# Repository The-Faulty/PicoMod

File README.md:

# PicoMod
PicoMod is an RP2040-based compute module with high density connectors allowing for its small 20mmx20mm form-factor.

# PicoMod Breakout
This is a breakout for PicoMod to allowing use on a standard breadboard.

# PicoMod Eject
Eject is the evolution of [Lyra](https://github.com/The_Faulty/Lyra) maintaining Lyra's small size while greatly improving the power and sensing abilities. Not only can eject ignite an e-match at apogee, it also contains a 9-DOF sensor suite and two servo outputs enabling TVC (thrust vector control) usage.

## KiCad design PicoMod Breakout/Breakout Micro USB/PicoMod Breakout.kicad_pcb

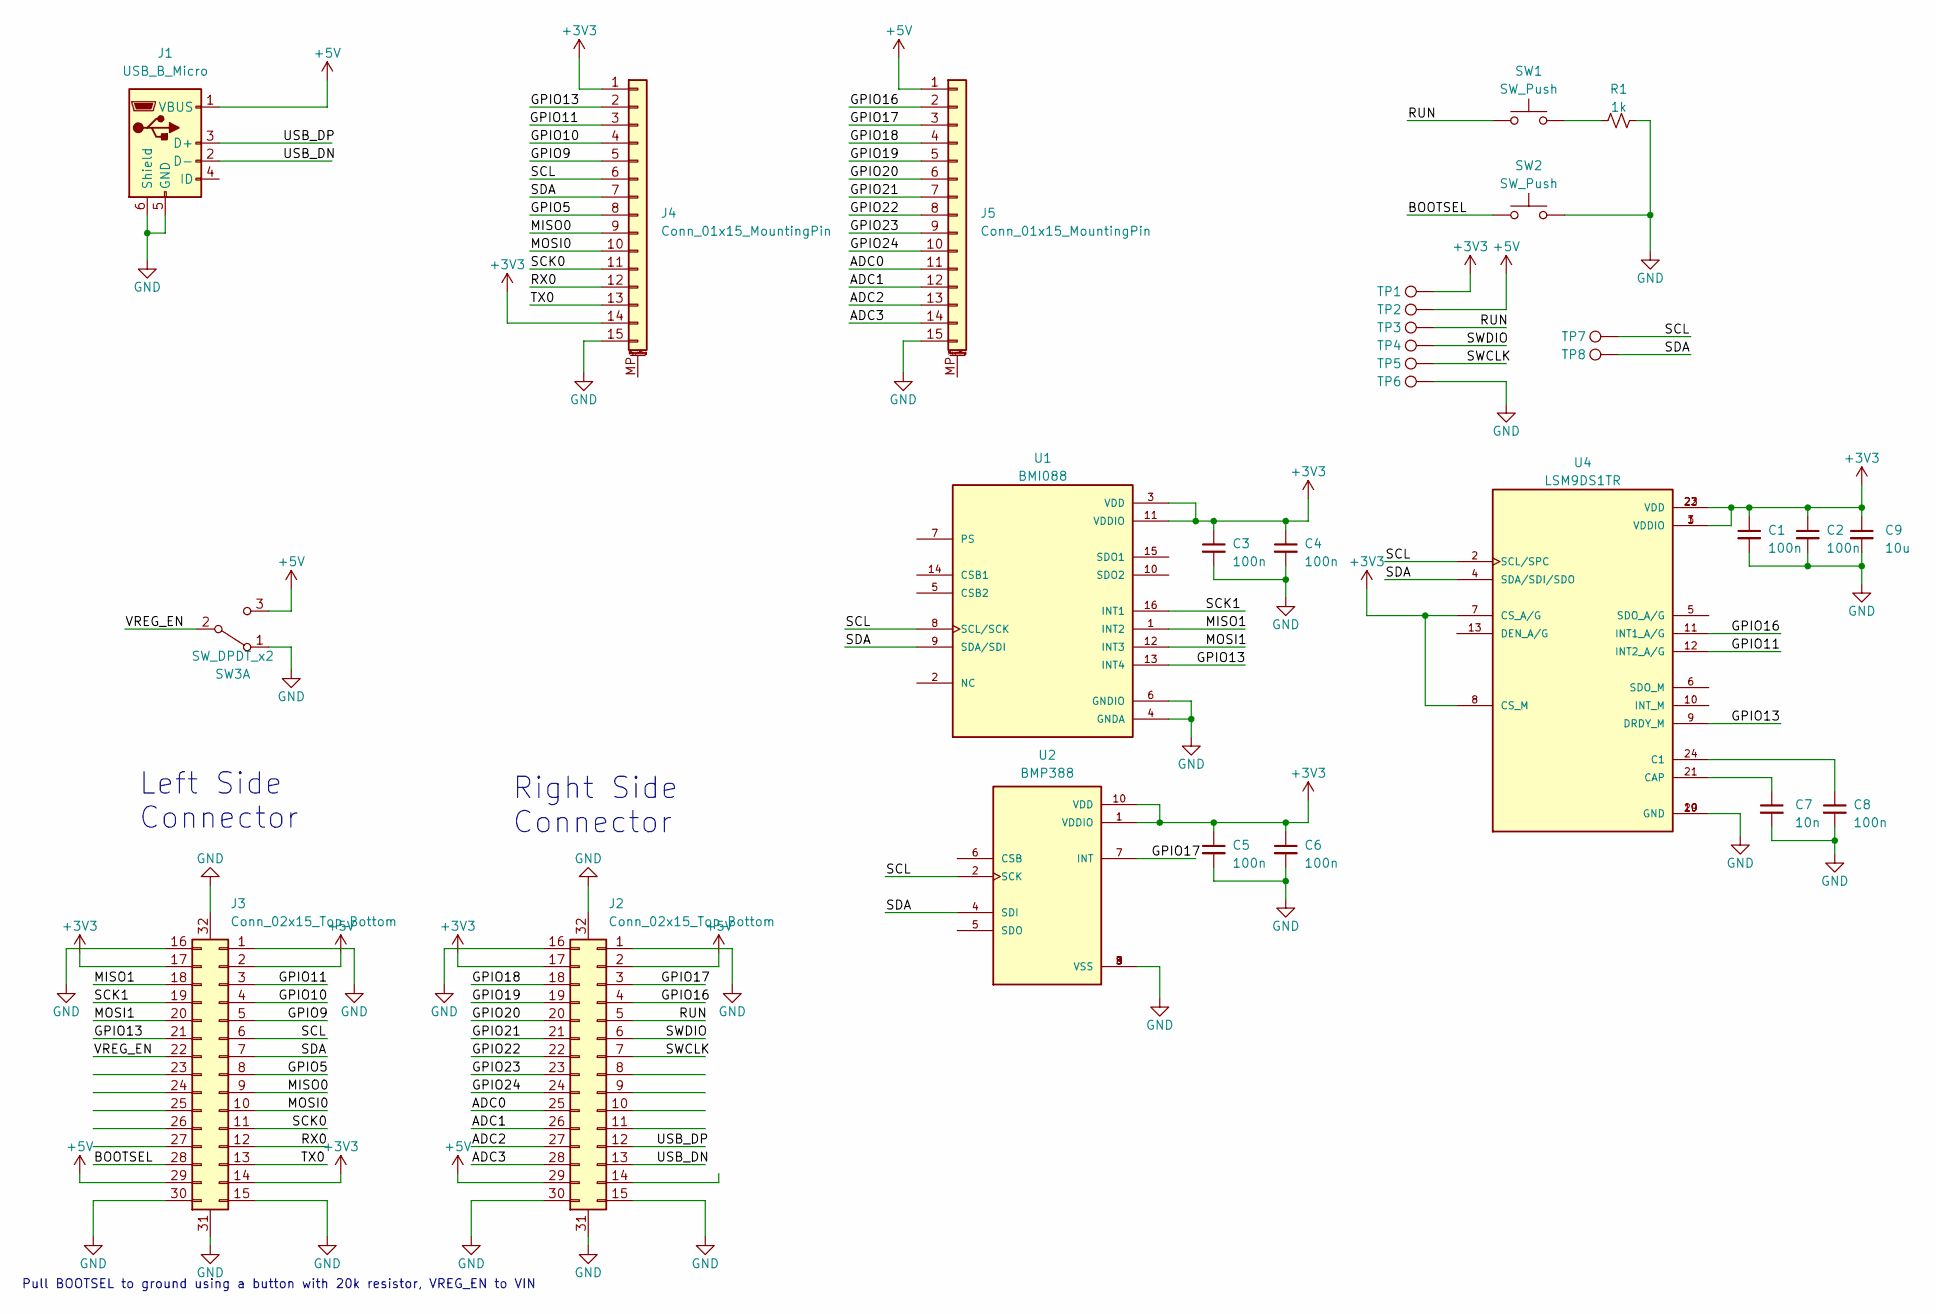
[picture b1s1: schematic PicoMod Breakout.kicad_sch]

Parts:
C1, C2, C3, C4, C5, C6, C8: 100n; C_0603_1608Metric
C7: 10n; C_0603_1608Metric
C9: 10u; C_0603_1608Metric
J1: USB_B_Micro; USB_Micro-B_Amphenol_10104110_Horizontal
J2, J3: Conn_02x15_Top_Bottom; TE-3-2363962-0_30x0.4mm_Recepticle
J4, J5: Conn_01x15_MountingPin; PinSocket_1x15_P2.54mm_Vertical
R1: 1k; R_0603_1608Metric_Pad0.98x0.95mm_HandSolder
SW1, SW2: SW_Push; PTS815 SJM 250
SW3: SW_DPDT_x2; SPDT_Switch_AYZ0102AGRLC
TP1, TP2, TP3, TP4, TP5, TP6, TP7, TP8: TestPoint; TestPoint_Loop_1.6x0.8mm
U1: BMI088; PQFN50P450X300X100-16N
U2: BMP388; PQFN50P200X200X80-10N; PARTREV 1.1
U4: LSM9DS1TR; PQFN43P300X350X102-24N; PARTREV 3

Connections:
+3V3: C1.1, C2.1, C3.1, C4.1, C5.1, C6.1, C9.1, J2.17, J3.14, J3.17, J4.1, J4.14, TP1.1, U1.3 (VDD), U1.11 (VDDIO), U2.1 (VDDIO), U2.10 (VDD), U4.1 (VDDIO), U4.3 (VDDIO), U4.7 (CS_A/G), U4.8 (CS_M), U4.22 (VDD), U4.23 (VDD)
+5V: J1.1 (VBUS), J2.2, J2.29, J3.2, J3.29, J5.1, SW3.3 (C), TP2.1
/ADC0: J2.25, J5.11
/ADC1: J2.26, J5.12
/ADC2: J2.27, J5.13
/ADC3: J2.28, J5.14
/BOOTSEL: J3.28, SW2.1
/GPIO5: J3.8, J4.8
/GPIO9: J3.5, J4.5
/GPIO10: J3.4, J4.4
/GPIO11: J3.3, J4.3, U4.12 (INT2_A/G)
/GPIO13: J3.21, J4.2, U1.13 (INT4), U4.9 (DRDY_M)
/GPIO16: J2.4, J5.2, U4.11 (INT1_A/G)
/GPIO17: J2.3, J5.3, U2.7 (INT)
/GPIO18: J2.18, J5.4
/GPIO19: J2.19, J5.5
/GPIO20: J2.20, J5.6
/GPIO21: J2.21, J5.7
/GPIO22: J2.22, J5.8
/GPIO23: J2.23, J5.9
/GPIO24: J2.24, J5.10
/MISO0: J3.9, J4.9
/MISO1: J3.18, U1.1 (INT2)
/MOSI0: J3.10, J4.10
/MOSI1: J3.20, U1.12 (INT3)
/RUN: J2.5, SW1.1, TP3.1
/RX0: J3.12, J4.12
/SCK0: J3.11, J4.11
/SCK1: J3.19, U1.16 (INT1)
/SCL: J3.6, J4.6, TP7.1, U1.8 (SCL/SCK), U2.2 (SCK), U4.2 (SCL/SPC)
/SDA: J3.7, J4.7, TP8.1, U1.9 (SDA/SDI), U2.4 (SDI), U4.4 (SDA/SDI/SDO)
/SWCLK: J2.7, TP5.1
/SWDIO: J2.6, TP4.1
/TX0: J3.13, J4.13
/USB_DN: J1.2 (D-), J2.13
/USB_DP: J1.3 (D+), J2.12
/VREG_EN: J3.22, SW3.2 (B)
GND: C1.2, C2.2, C3.2, C4.2, C5.2, C6.2, C7.2, C8.2, C9.2, J1.5 (GND), J1.6 (Shield), J2.1, J2.15, J2.16, J2.30, J2.31 (Pin_30), J2.32 (Pin_30), J3.1, J3.15, J3.16, J3.30, J3.31 (Pin_30), J3.32 (Pin_30), J4.15, J5.15, R1.2, SW2.2, SW3.1 (A), TP6.1, U1.4 (GNDA), U1.6 (GNDIO), U2.3 (VSS), U2.8 (VSS), U2.9 (VSS), U4.19 (GND), U4.20 (GND)
unnamed: R1.1, SW1.2
unnamed: C8.1, U4.24 (C1)
unnamed: C7.1, U4.21 (CAP)

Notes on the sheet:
Left Side Connector
Right Side Connector
Pull BOOTSEL to ground using a button with 20k resistor, VREG_EN to VIN

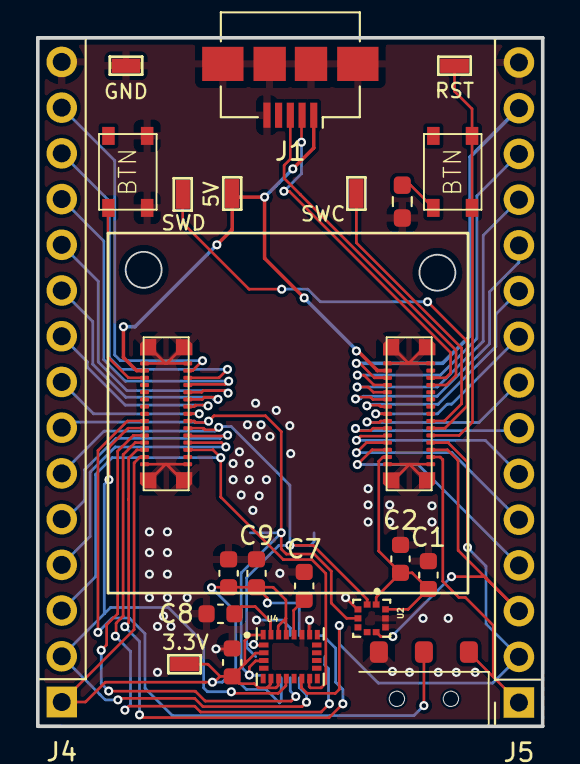
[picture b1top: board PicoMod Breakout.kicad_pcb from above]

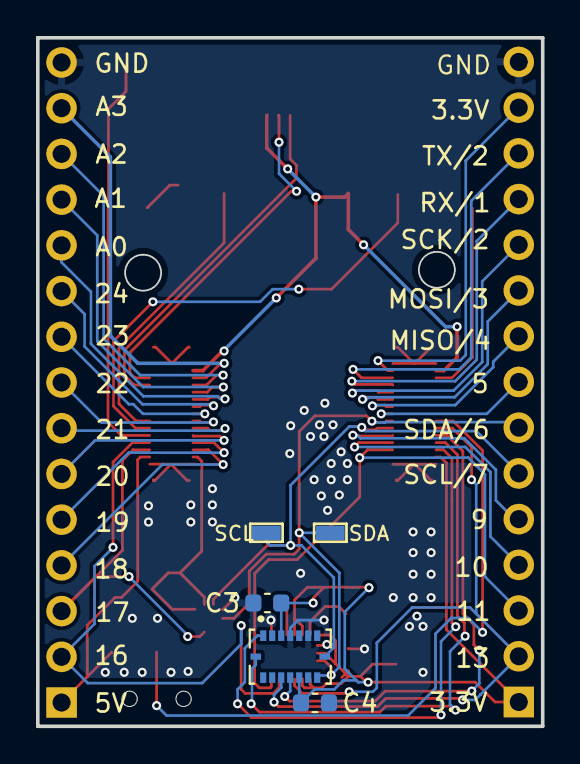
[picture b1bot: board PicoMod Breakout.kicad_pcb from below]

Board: 2 copper layers, 28.0 x 38.3 mm, 29 parts (5 on the bottom side), 41 nets.

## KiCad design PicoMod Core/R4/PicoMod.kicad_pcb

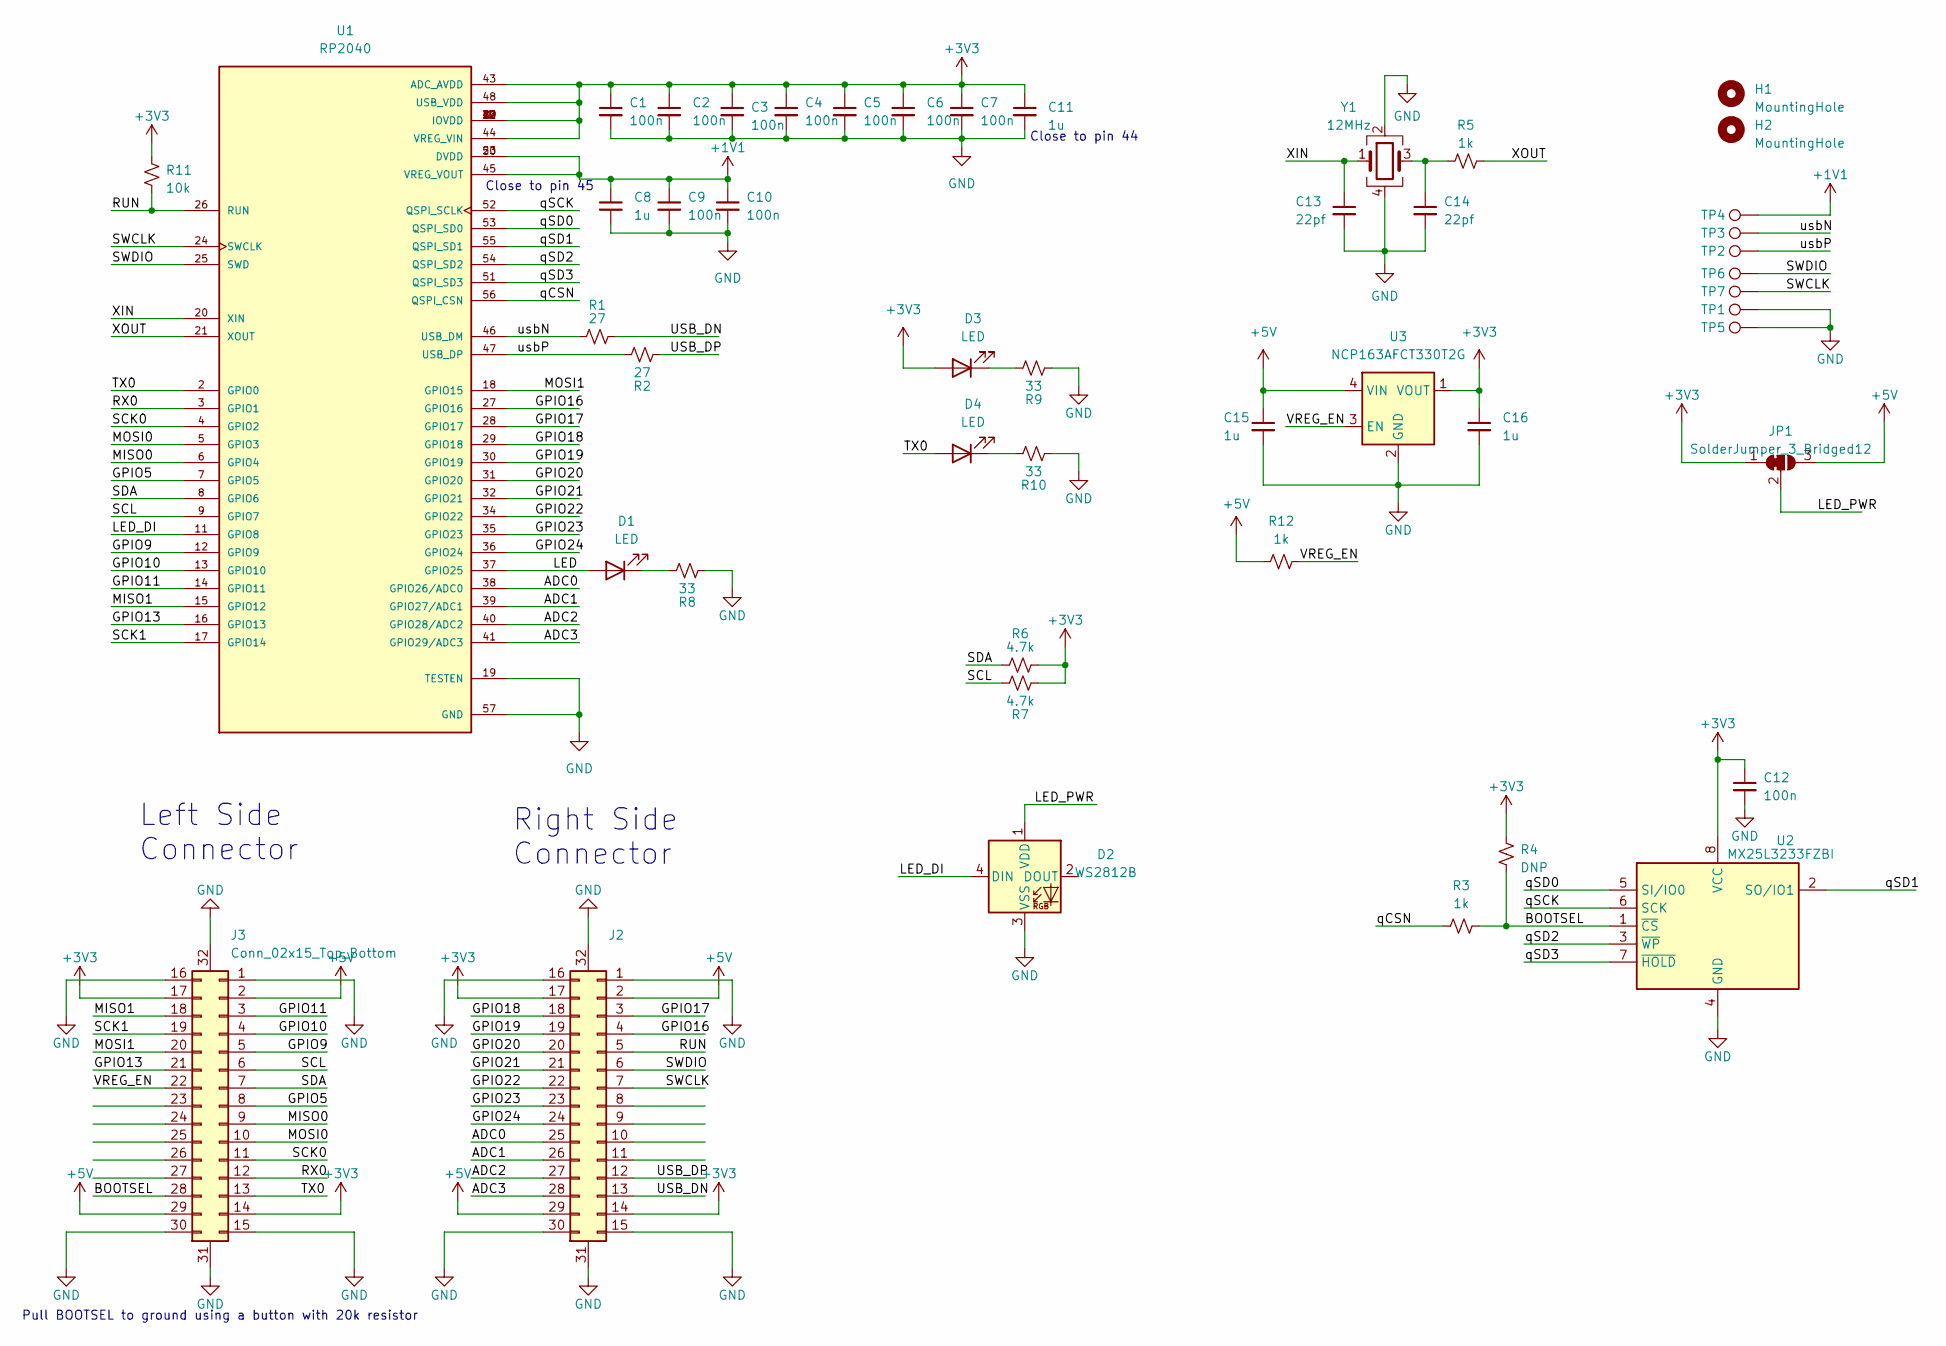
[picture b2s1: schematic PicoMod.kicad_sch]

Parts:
C1, C2, C3, C4, C5, C6, C7, C9, C10, C12: 100n; C_0603_1608Metric
C8, C11, C15, C16: 1u; C_0603_1608Metric
C13, C14: 22pf; C_0603_1608Metric
D1, D3, D4: LED; LED_0603_1608Metric
D2: WS2812B; LED_WS2812B_PLCC4_2.0x2.0mm_P0.4mm
H1, H2: MountingHole; MountingHole_2mm_M2
J2, J3: Conn_02x15_Top_Bottom; TE-3-2363962-0_30x0.4mm_Plug
JP1: SolderJumper_3_Bridged12; SolderJumper-3_P1.3mm_Open_RoundedPad1.0x1.5mm
R1, R2: 27; R_0402_1005Metric
R3, R5, R12: 1k; R_0402_1005Metric
R4: DNP; R_0603_1608Metric
R6, R7: 4.7k; R_0603_1608Metric
R8, R9, R10: 33; R_0402_1005Metric
R11: 10k; R_0603_1608Metric
TP1: TestPoint; TestPoint_Loop_1.6x0.8mm
TP2, TP3, TP4, TP5, TP6, TP7: TestPoint; TestPoint_Pad_D1.0mm
U1: RP2040; QFN40P700X700X90-57N; PARTREV 1.6.1
U2: MX25L3233FZBI; SON80P400X300X60-10N
U3: NCP163AFCT330T2G; OnSemi_XDFN4-1EP_1.0x1.0mm_EP0.52x0.52mm
Y1: 12MHz; Crystal_SMD_SeikoEpson_TSX3225-4Pin_3.2x2.5mm

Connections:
+1V1: C8.1, C9.1, C10.1, TP4.1, U1.23 (DVDD), U1.45 (VREG_VOUT), U1.50 (DVDD)
+3V3: C1.1, C2.1, C3.1, C4.1, C5.1, C6.1, C7.1, C11.1, C12.1, C16.1, D3.2 (A), J2.14, J2.17, J3.14, J3.17, JP1.1 (A), R4.2, R6.2, R7.2, R11.2, U1.1 (IOVDD), U1.10 (IOVDD), U1.22 (IOVDD), U1.33 (IOVDD), U1.42 (IOVDD), U1.43 (ADC_AVDD), U1.44 (VREG_VIN), U1.48 (USB_VDD), U1.49 (IOVDD), U2.8 (VCC), U3.1 (VOUT)
+5V: C15.1, J2.2, J2.29, J3.2, J3.29, JP1.3 (B), R12.1, U3.4 (VIN)
/ADC0: J2.25, U1.38 (GPIO26/ADC0)
/ADC1: J2.26, U1.39 (GPIO27/ADC1)
/ADC2: J2.27, U1.40 (GPIO28/ADC2)
/ADC3: J2.28, U1.41 (GPIO29/ADC3)
/BOOTSEL: J3.28, R3.2, R4.1, U2.1 (~CS)
/GPIO5: J3.8, U1.7 (GPIO5)
/GPIO9: J3.5, U1.12 (GPIO9)
/GPIO10: J3.4, U1.13 (GPIO10)
/GPIO11: J3.3, U1.14 (GPIO11)
/GPIO13: J3.21, U1.16 (GPIO13)
/GPIO16: J2.4, U1.27 (GPIO16)
/GPIO17: J2.3, U1.28 (GPIO17)
/GPIO18: J2.18, U1.29 (GPIO18)
/GPIO19: J2.19, U1.30 (GPIO19)
/GPIO20: J2.20, U1.31 (GPIO20)
/GPIO21: J2.21, U1.32 (GPIO21)
/GPIO22: J2.22, U1.34 (GPIO22)
/GPIO23: J2.23, U1.35 (GPIO23)
/GPIO24: J2.24, U1.36 (GPIO24)
/LED: D1.2 (A), U1.37 (GPIO25)
/LED_DI: D2.4 (DIN), U1.11 (GPIO8)
/LED_PWR: D2.1 (VDD), JP1.2 (C)
/MISO0: J3.9, U1.6 (GPIO4)
/MISO1: J3.18, U1.15 (GPIO12)
/MOSI0: J3.10, U1.5 (GPIO3)
/MOSI1: J3.20, U1.18 (GPIO15)
/RUN: J2.5, R11.1, U1.26 (RUN)
/RX0: J3.12, U1.3 (GPIO1)
/SCK0: J3.11, U1.4 (GPIO2)
/SCK1: J3.19, U1.17 (GPIO14)
/SCL: J3.6, R7.1, U1.9 (GPIO7)
/SDA: J3.7, R6.1, U1.8 (GPIO6)
/SWCLK: J2.7, TP7.1, U1.24 (SWCLK)
/SWDIO: J2.6, TP6.1, U1.25 (SWD)
/TX0: D4.2 (A), J3.13, U1.2 (GPIO0)
/USB_DN: J2.13, R1.2
/USB_DP: J2.12, R2.2
/VREG_EN: J3.22, R12.2, U3.3 (EN)
/XIN: C13.1, U1.20 (XIN), Y1.1
/XOUT: R5.1, U1.21 (XOUT)
/qCSN: R3.1, U1.56 (QSPI_CSN)
/qSCK: U1.52 (QSPI_SCLK), U2.6 (SCK)
/qSD0: U1.53 (QSPI_SD0), U2.5 (SI/IO0)
/qSD1: U1.55 (QSPI_SD1), U2.2 (SO/IO1)
/qSD2: U1.54 (QSPI_SD2), U2.3 (~WP)
/qSD3: U1.51 (QSPI_SD3), U2.7 (~HOLD)
/usbN: R1.1, TP3.1, U1.46 (USB_DM)
/usbP: R2.1, TP2.1, U1.47 (USB_DP)
GND: C1.2, C2.2, C3.2, C4.2, C5.2, C6.2, C7.2, C8.2, C9.2, C10.2, C11.2, C12.2, C13.2, C14.2, C15.2, C16.2, D2.3 (VSS), J2.1, J2.15, J2.16, J2.30, J2.31 (Pin_30), J2.32 (Pin_30), J3.1, J3.15, J3.16, J3.30, J3.31 (Pin_30), J3.32 (Pin_30), R8.2, R9.2, R10.2, TP1.1, TP5.1, U1.19 (TESTEN), U1.57 (GND), U2.4 (GND), U3.2 (GND), Y1.2, Y1.4
unnamed: C14.1, R5.2, Y1.3
unnamed: D1.1 (K), R8.1
unnamed: D3.1 (K), R9.1
unnamed: D4.1 (K), R10.1

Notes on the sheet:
Close to pin 45
Left Side Connector
Close to pin 44
Right Side Connector
Pull BOOTSEL to ground using a button with 20k resistor

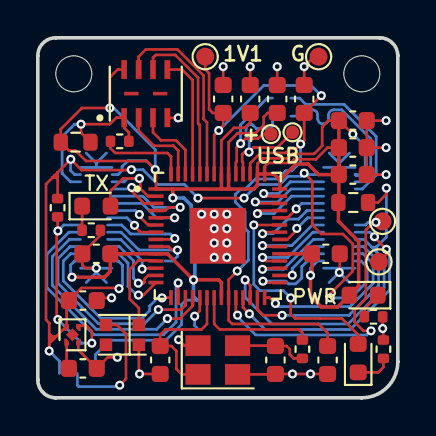
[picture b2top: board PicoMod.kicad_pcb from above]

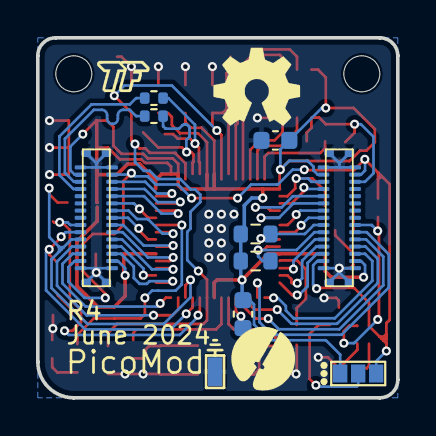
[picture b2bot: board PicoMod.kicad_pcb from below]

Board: 2 copper layers, 20.0 x 20.0 mm, 48 parts (10 on the bottom side), 56 nets.

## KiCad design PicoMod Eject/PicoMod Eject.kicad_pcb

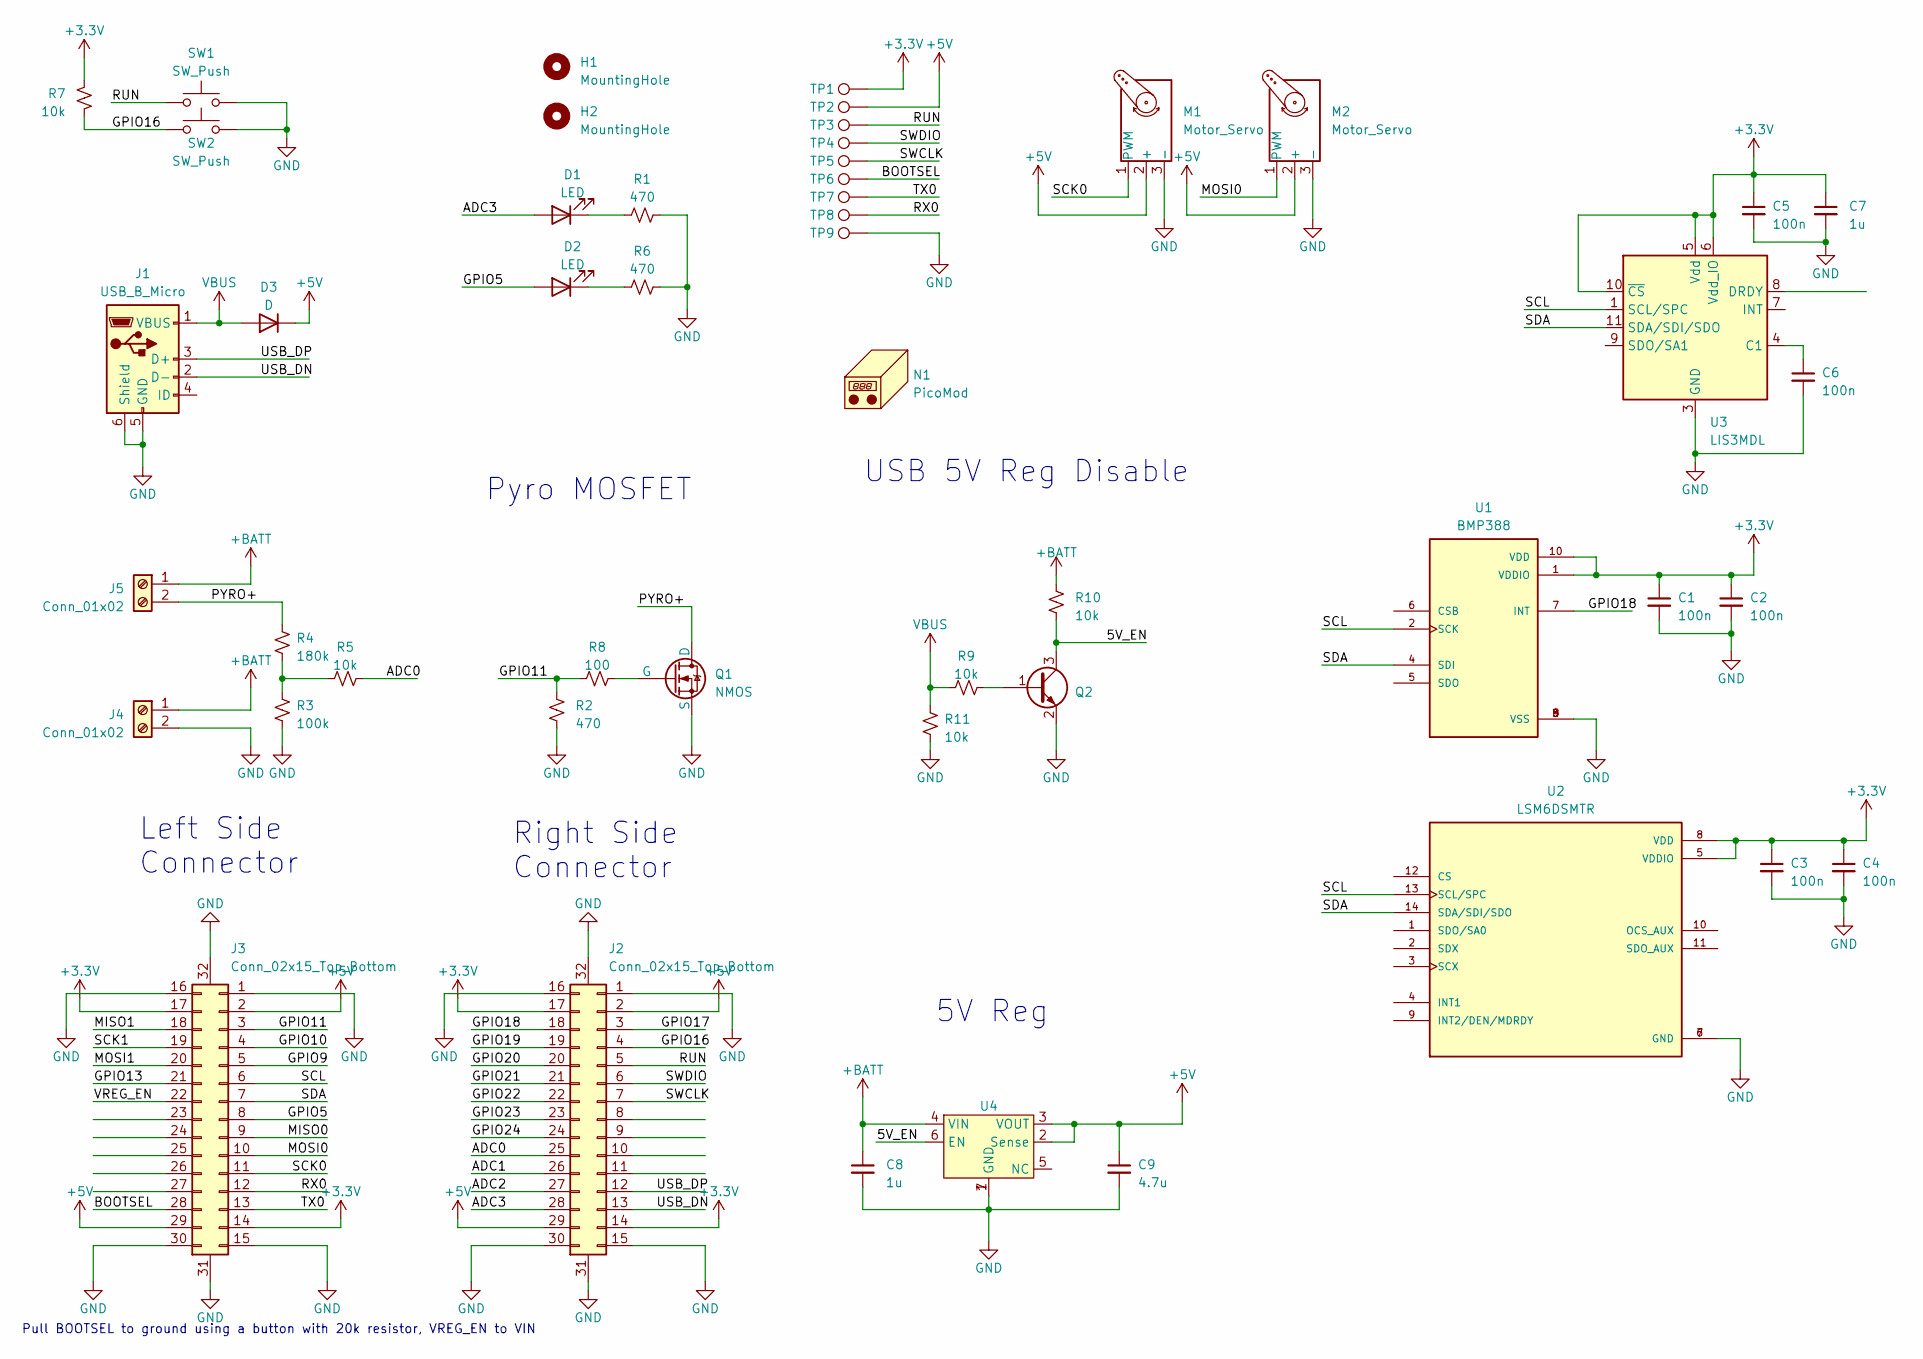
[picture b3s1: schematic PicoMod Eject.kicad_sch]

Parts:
C1, C2, C3, C4, C5, C6: 100n; C_0603_1608Metric
C7, C8: 1u; C_0603_1608Metric
C9: 4.7u; C_0603_1608Metric
D1, D2: LED; LED_0603_1608Metric
D3: D; D_SOD-523
H1, H2: MountingHole; MountingHole_2mm_M2
J1: USB_B_Micro; USB_Micro-B_Amphenol_10104110_Horizontal
J2, J3: Conn_02x15_Top_Bottom; TE-3-2363962-0_30x0.4mm_Recepticle
J4, J5: Conn_01x02; TerminalBlock_TE_282834-2_1x02_P2.54mm_Horizontal
M1, M2: Motor_Servo; 1x3-Servo-Connector-1.2x2mm
N1: PicoMod; OSHW-Logo_7.5x8mm_SilkScreen
Q1: NMOS; MOSFET_SI8406DB-T2-E1
Q2: SOT-323_SC-70
R1, R6: 470; R_0402_1005Metric
R2: 470; R_0603_1608Metric_Pad0.98x0.95mm_HandSolder
R3: 100k; R_0402_1005Metric_Pad0.72x0.64mm_HandSolder
R4: 180k; R_0402_1005Metric_Pad0.72x0.64mm_HandSolder
R5, R9, R11: 10k; R_0603_1608Metric_Pad0.98x0.95mm_HandSolder
R7, R10: 10k; R_0603_1608Metric
R8: 100; R_0603_1608Metric_Pad0.98x0.95mm_HandSolder
SW1, SW2: SW_Push; PTS815 SJM 250
TP1, TP2, TP3, TP4, TP5, TP6, TP7, TP8, TP9: TestPoint; TestPoint_Loop_1.6x0.8mm
U1: BMP388; PQFN50P200X200X80-10N; PARTREV 1.1
U2: LSM6DSMTR; PQFN50P300X250X86-14N; PARTREV Rev 7
U3: LIS3MDL; LGA-12_2x2mm_P0.5mm
U4: LDL212PU-5V-Regulator

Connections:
+3V3: C1.1, C2.1, C3.1, C4.1, C5.1, C7.1, J2.14, J2.17, J3.14, J3.17, R7.1, TP1.1, U1.1 (VDDIO), U1.10 (VDD), U2.5 (VDDIO), U2.8 (VDD), U3.5 (Vdd), U3.6 (Vdd_IO), U3.10 (~CS)
+5V: C9.1, D3.1 (K), J2.2, J2.29, J3.2, J3.29, M1.2 (+), M2.2 (+), TP2.1, U4.2 (Sense), U4.3 (VOUT)
+BATT: C8.1, J4.1, J5.1, R10.2, U4.4 (VIN)
/5V_EN: Q2.3 (C), R10.1, U4.6 (EN)
/ADC0: J2.25, R5.1
/ADC1: J2.26
/ADC2: J2.27
/ADC3: D1.2 (A), J2.28
/BOOTSEL: J3.28, TP6.1
/GPIO5: D2.2 (A), J3.8
/GPIO9: J3.5
/GPIO10: J3.4
/GPIO11: J3.3, R2.2, R8.2
/GPIO13: J3.21
/GPIO16: J2.4, R7.2, SW2.1
/GPIO17: J2.3
/GPIO18: J2.18, U1.7 (INT)
/GPIO19: J2.19
/GPIO20: J2.20
/GPIO21: J2.21
/GPIO22: J2.22
/GPIO23: J2.23
/GPIO24: J2.24
/MISO0: J3.9
/MISO1: J3.18
/MOSI0: J3.10, M2.1 (PWM)
/MOSI1: J3.20
/PYRO+: J5.2, Q1.1 (D), R4.2
/RUN: J2.5, SW1.1, TP3.1
/RX0: J3.12, TP8.1
/SCK0: J3.11, M1.1 (PWM)
/SCK1: J3.19
/SCL: J3.6, U1.2 (SCK), U2.13 (SCL/SPC), U3.1 (SCL/SPC)
/SDA: J3.7, U1.4 (SDI), U2.14 (SDA/SDI/SDO), U3.11 (SDA/SDI/SDO)
/SWCLK: J2.7, TP5.1
/SWDIO: J2.6, TP4.1
/TX0: J3.13, TP7.1
/USB_DN: J1.2 (D-), J2.13
/USB_DP: J1.3 (D+), J2.12
/VREG_EN: J3.22
GND: C1.2, C2.2, C3.2, C4.2, C5.2, C6.2, C7.2, C8.2, C9.2, J1.5 (GND), J1.6 (Shield), J2.1, J2.15, J2.16, J2.30, J2.31 (Pin_30), J2.32 (Pin_30), J3.1, J3.15, J3.16, J3.30, J3.31 (Pin_30), J3.32 (Pin_30), J4.2, M1.3 (-), M2.3 (-), Q1.3 (S), Q2.2 (E), R1.1, R2.1, R3.1, R6.1, R11.2, SW1.2, SW2.2, TP9.1, U1.3 (VSS), U1.8 (VSS), U1.9 (VSS), U2.6 (GND), U2.7 (GND), U3.2 (GND), U3.3 (GND), U3.12 (GND), U4.1 (GND), U4.7 (GND)
unnamed: D1.1 (K), R1.2
unnamed: D2.1 (K), R6.2
unnamed: Q1.2 (G), R8.1
unnamed: Q2.1 (B), R9.1
unnamed: R3.2, R4.1, R5.2
unnamed: C6.1, U3.4 (C1)
VBUS: D3.2 (A), J1.1 (VBUS), R9.2, R11.1

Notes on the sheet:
Left Side Connector
USB 5V Reg Disable
Pyro MOSFET
Right Side Connector
5V Reg
Pull BOOTSEL to ground using a button with 20k resistor, VREG_EN to VIN

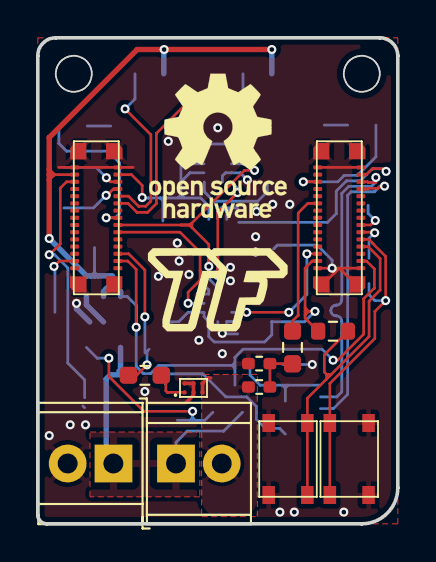
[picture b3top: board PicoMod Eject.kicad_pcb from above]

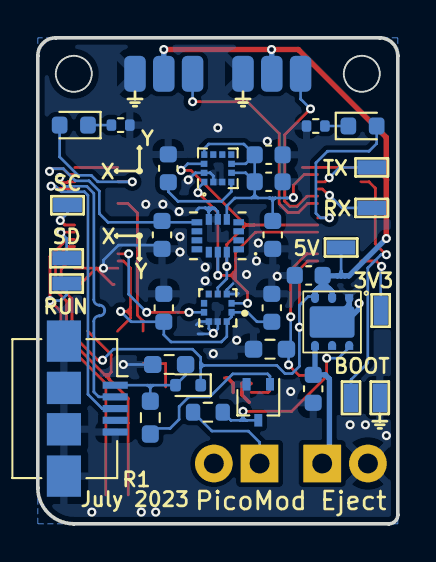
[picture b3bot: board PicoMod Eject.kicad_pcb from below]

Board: 2 copper layers, 20.0 x 27.0 mm, 50 parts (35 on the bottom side), 31 nets.

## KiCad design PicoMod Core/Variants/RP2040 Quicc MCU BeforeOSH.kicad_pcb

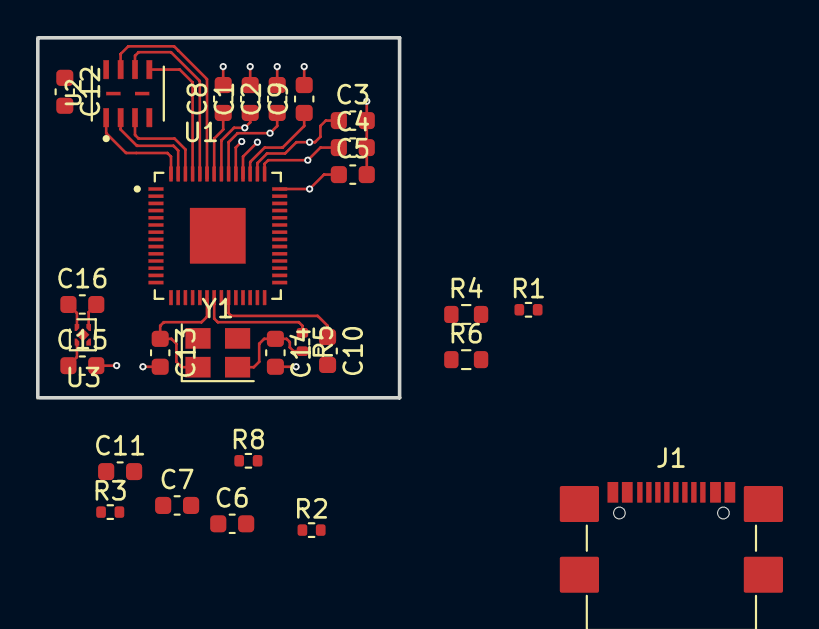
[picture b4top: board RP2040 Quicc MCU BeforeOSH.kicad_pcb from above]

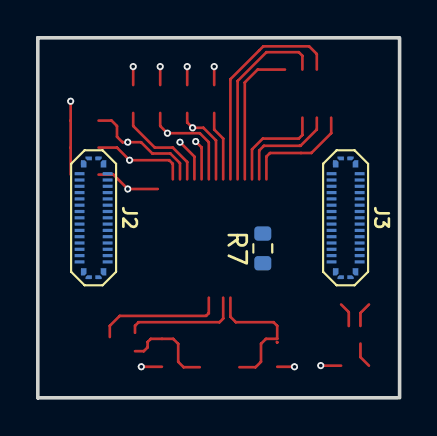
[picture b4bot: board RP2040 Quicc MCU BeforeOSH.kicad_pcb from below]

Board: 2 copper layers, 20.1 x 20.0 mm, 31 parts (3 on the bottom side), 19 nets.

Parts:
C1, C2, C3, C4, C5, C6, C7, C9, C10, C12: 100n; C_0603_1608Metric
C8, C11, C15, C16: 1u; C_0603_1608Metric
C13, C14: 22pf; C_0603_1608Metric
J1: USB_C_Receptacle_USB2.0; USB_C_Receptacle_GCT_USB4110
J2, J3: Conn_02x15_Top_Bottom; 245861030004829+
R1, R2, R8: 27.4; R_0402_1005Metric
R3, R5: 1k; R_0402_1005Metric
R4: 10k; R_0603_1608Metric
R6, R7: 4.7k; R_0603_1608Metric
U1: RP2040; QFN40P700X700X90-57N
U2: locked; SON80P400X300X60-10N
U3: NCP163AFCT330T2G; OnSemi_XDFN4-1EP_1.0x1.0mm_EP0.52x0.52mm
Y1: 12MHz; Crystal_SMD_SeikoEpson_TSX3225-4Pin_3.2x2.5mm

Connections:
+3V3: C1.1, C2.1, C3.1, C4.1, C5.1, C6.1, C7.1, C11.1, C12.1, C16.1, R4.2, U1.1 (IOVDD), U1.10 (IOVDD), U1.22 (IOVDD), U1.33 (IOVDD), U1.42 (IOVDD), U1.43 (ADC_AVDD), U1.44 (VREG_VIN), U1.48 (USB_VDD), U1.49 (IOVDD), U2.8 (VCC), U3.1 (VOUT)
+5V: C15.1, J1.A4 (VBUS), J1.A9 (VBUS), J1.B4 (VBUS), J1.B9 (VBUS), U3.4 (VIN)
/USB_DM: J1.A7 (D-), J1.B7 (D-), R1.2
/USB_DP: J1.A6 (D+), J1.B6 (D+), R2.2
/XIN: C13.1, U1.20 (XIN), Y1.1
/XOUT: R5.1, U1.21 (XOUT)
/qCSN: R3.2, R4.1, U1.56 (QSPI_CSN), U2.1 (~CS)
/qSCK: U1.52 (QSPI_SCLK), U2.6 (SCK)
/qSD0: U1.53 (QSPI_SD0), U2.5 (SI/IO0)
/qSD1: U1.55 (QSPI_SD1), U2.2 (SO/IO1)
/qSD2: U1.54 (QSPI_SD2), U2.3 (~WP)
/qSD3: U1.51 (QSPI_SD3), U2.7 (~HOLD)
GND: C1.2, C2.2, C3.2, C4.2, C5.2, C6.2, C7.2, C8.2, C9.2, C10.2, C11.2, C12.2, C13.2, C14.2, C15.2, C16.2, J1.A1 (GND), J1.A12 (GND), J1.B1 (GND), J1.B12 (GND), J1.S1 (SHIELD), U1.19 (TESTEN), U1.57 (GND), U2.4 (GND), U3.2 (GND)
unnamed: C8.1, C9.1, C10.1, U1.23 (DVDD), U1.45 (VREG_VOUT), U1.50 (DVDD)
unnamed: C14.1, R5.2, Y1.2
unnamed: R1.1, U1.46 (USB_DM)
unnamed: R2.1, U1.47 (USB_DP)
unnamed: R6.2, U1.6 (GPIO4)
unnamed: R7.2, U1.7 (GPIO5)

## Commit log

2023-06-07 R2 Upload
2023-09-25 Added other boards and readme
2024-08-21 Updated with R4 of core board and micro usb breakout
